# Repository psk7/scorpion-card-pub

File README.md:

## Контроллер периферии для ретро-компьютера Scorpion ZS-256

## Ревизия B:

Подключается к разъему периферии платы компьютера. Позволяет использовать USB клавиатуры, мыши, джойстики, геймпады.

## Ревизия С:
                 
Автономный контроллер USB клавиатуры и геймпада. Не привязан к разъему Scorpion и может
быть использован с любым Spectrum совместимым компьютером, использующим стандартную ZX клавиатуру, но
не имеет поддержки Kempston Mouse и возможностей, обеспечиваемых периферийным разъемом ZS-Scorpion за исключением
клавиатуры и Kempston джойстика.

## Уже реализовано:
- USB-хост: поддержка клавиатур, HID мышей, HID джойстиков/геймпадов, USB хабов
- USB-устройство: подключается к PC, возможно взаимодействие PC со Spectrum
- Безвейтовая ZX-клавиатура с произвольными раскладками, настраиваемыми с PC 
- Reset, Magic с клавиатуры
- Настраиваемые раскладки USB джойстика/геймпада, возможно задействование до 16 кнопок 
- Регенерация синхросмеси. Никаких больше перемычек/разрезов на плате. PAL кодер теперь дает нормальный цветной сигнал
- С доп. платой (в слот шины) USB мышь превращается в Kempston mouse
- Транзитом передает на гребенки: RGB сигнал (с выбором джампером оригинальная/регенерированная синхросмесь), стерео-аудио, моно-аудио, оригинальный видео сигнал, магнитофонный вход/выход, RS-232
- Единая точка подключения питания
- Подключение внешнего джойстика (от Spectrum)
- Настраиваемое отображение кнопок USB джойстика на кнопки ZX клавиатуры/Kempston Joystick
- Управление/индикация на клавиатуре турбой через двухпиновую колодку скорпиона
- Захват centronix в передача на PC
- Проигрыватель tap/tzx с PC через USB порт в Спектрум (`LOAD ""`)
- Транзитная передача с RS232 Скорпиона 
- Поддержка нескольких джойстиков/геймпадов

### Планируется:
- Настройки контроллера (раскладки, мышь, джойстик) через доп. плату нативным приложением для скорпиона

### Недостатки: :smile:
- Нет поддержки PS/2 мышей и клавиатур

## Ревизия А: (Устаревшая)

ВНИМАНИЕ!!! Эта ревизия НЕ РЕКОМЕНДУЕТСЯ К ИЗГОТОВЛЕНИЮ. К сожалению, при проектировании был выбран микроконтроллер не позволяющий реализовать все желаемое по причине нехватки ОЗУ. Готовится к публикации ревизия B, в которой эта проблема устранена.

Файлы для производства удалены из репозитория.

## Содержимое репозитория:
### revB
- cpld - Прошивки микросхем EPM3064
- gerbers - Файлы для производства плат

### revC
- kbd - Прошивка клавиатурной матрицы
- kicad - Проект плат
- atmega - Прошивка управляющего контроллера

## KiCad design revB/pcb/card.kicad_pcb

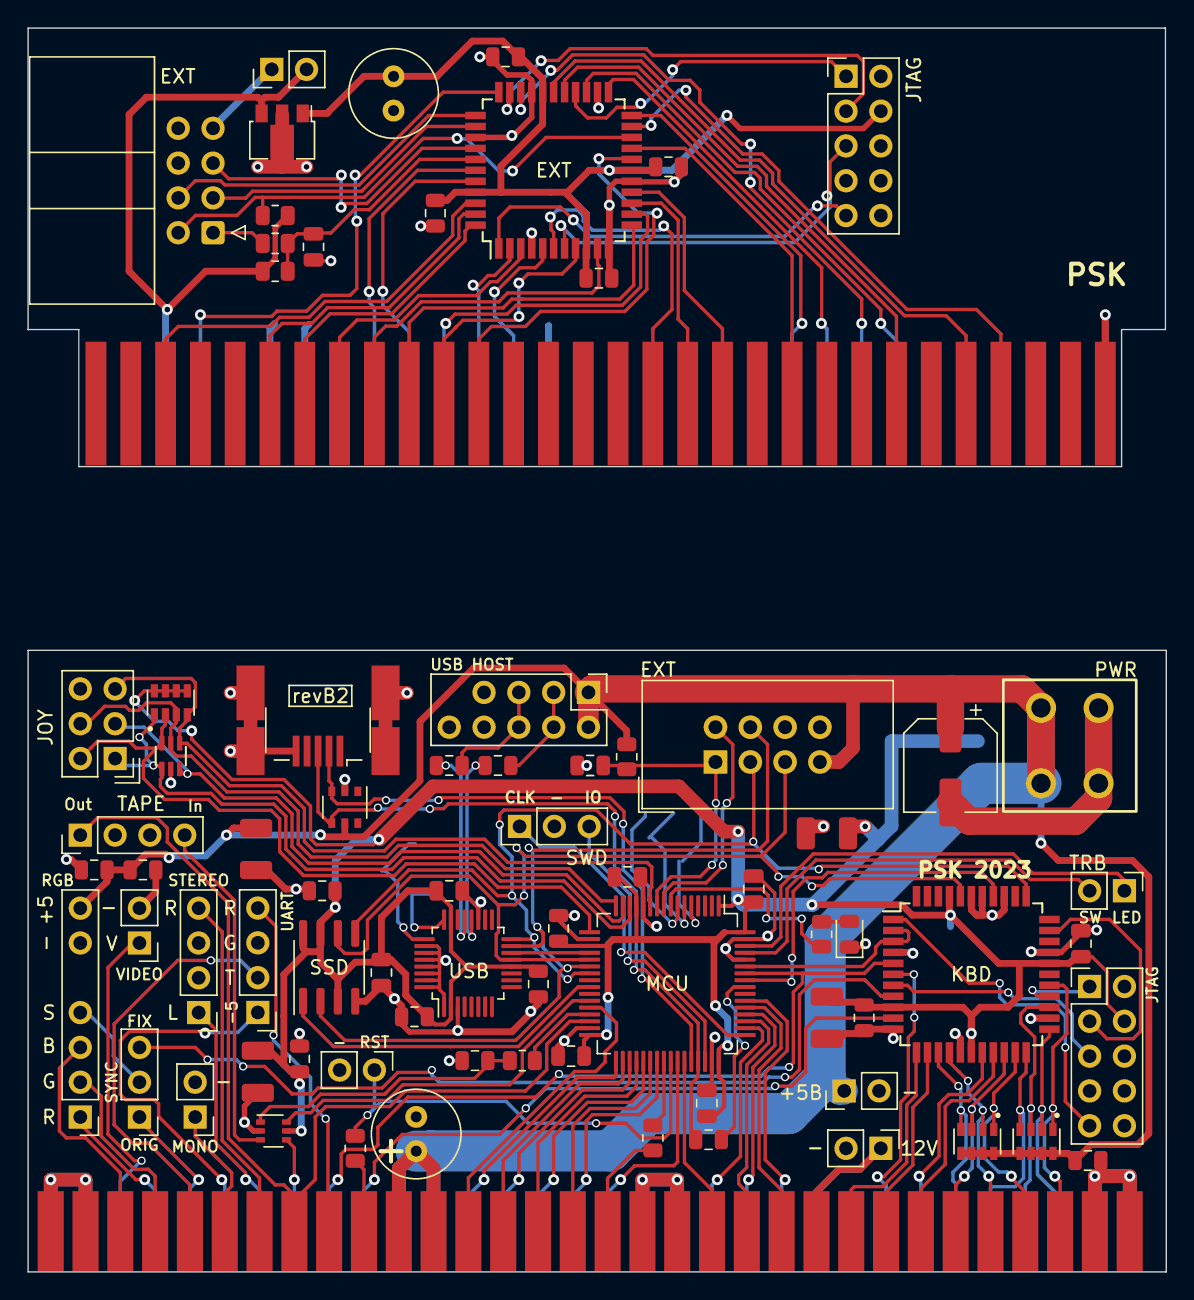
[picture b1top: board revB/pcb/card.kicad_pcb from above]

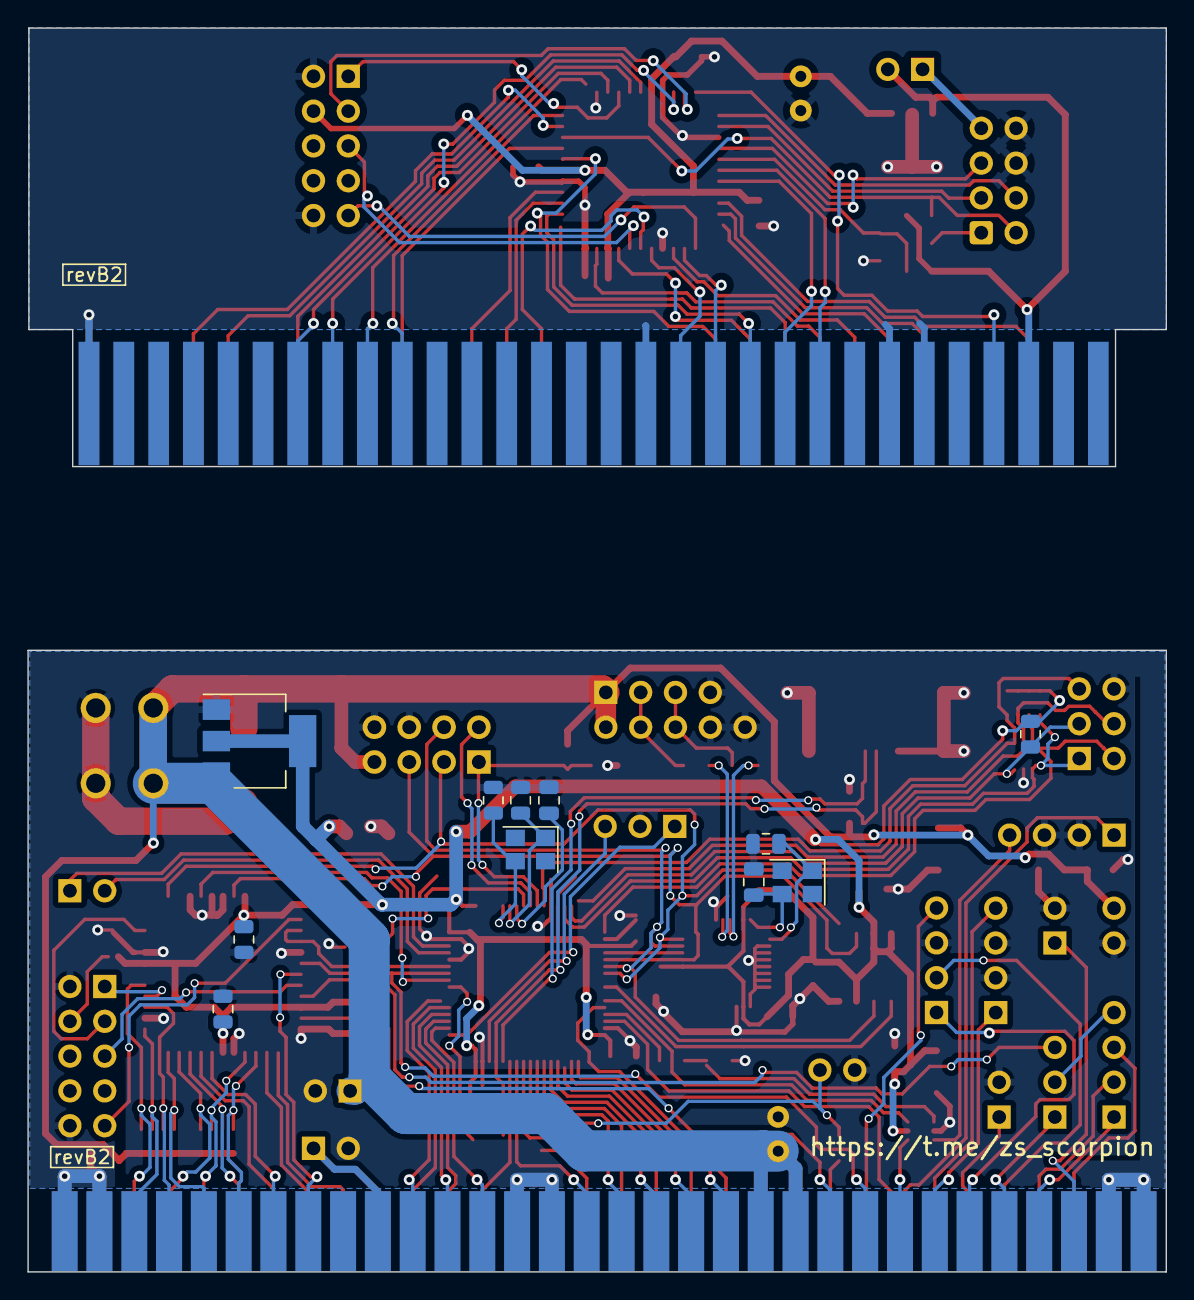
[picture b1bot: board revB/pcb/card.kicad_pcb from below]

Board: 2 copper layers, 83.1 x 45.4 mm, 88 parts (11 on the bottom side), 130 nets.

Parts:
C1, C2, C33, C34: 9p; C_0805_2012Metric
C3, C5, C7, C8, C9, C10, C11, C14, C15, C17, C21, C22, C23, C26, C27, C28, C29, C30, C32, C35, C36: C; C_0805_2012Metric
C4, C12, C18: 4.7uF; C_0805_2012Metric
C6, C24, C25, C31: CP; CP_EIA-3528-12_Kemet-T
C13: CP; CP_Elec_6.3x7.7
C16, C20: CP; C_Radial_D6.3mm_H11.0mm_P2.50mm
C19: 0.1uF; C_0805_2012Metric
D1: LED; LED_0805_2012Metric
J1: USB_B_Mini; usb_mini
J2: SWD; PinHeader_1x03_P2.54mm_Vertical
J3: Conn_01x04; PinHeader_2x05_P2.54mm_Vertical
J4, J6, J7: Conn_01x02; PinHeader_1x02_P2.54mm_Vertical
J5, J10: Conn_01x04; PinHeader_1x04_P2.54mm_Vertical
J8: Conn_01x07_RGB; PinHeader_1x07_P2.54mm_Vertical_RGB
J9: Conn_01x03; PinHeader_1x03_P2.54mm_Vertical
J11: Conn_01x08; IDC-Header_2x04_P2.54mm_Vertical
J12, J15: JTAG; PinHeader_2x05_P2.54mm_Vertical
J13: Conn_02x03_Odd_Even; PinHeader_2x03_P2.54mm_Vertical
J14, J19: +5В; PinHeader_1x02_P2.54mm_Vertical
J16: PWR; pwr
J17: EXT; IDC-Header_2x04_P2.54mm_Horizontal
J18: UART; PinHeader_1x04_P2.54mm_Vertical
J20: 3V3; PinHeader_1x02_P2.54mm_Vertical
J21: Conn_01x01_Male; PinHeader_1x02_P2.54mm_Vertical
R1, R2: 33; R_0805_2012Metric
R3: 1k5; R_0805_2012Metric
R4, R7: 0; R_0805_2012Metric
R5, R11: 1K; R_0805_2012Metric
R6, R12: 1k; R_0805_2012Metric
R8: 1k2; R_0805_2012Metric
R9, R13: 250; R_0805_2012Metric
R14: -; R_0805_2012Metric
RN1, RN2, RN3: 4x1k2; RESCAF80P320X160X60-8N
U1: STM32F103R8; LQFP-64_10x10mm_P0.5mm
U2: EPM3064; TQFP-44_10x10mm_P0.8mm
U3: MAX3421EEHJ+T; LQFP-32_5x5mm_P0.5mm
U4: IP4220CZ6; TSOP-6_1.65x3.05mm_P0.95mm
U5: 25LC256T; SOIC-8_3.9x4.9mm_P1.27mm
U7: EXT; TQFP-44_10x10mm_P0.8mm
U8: L78L33; SOT-89-3
U9: SMF05CT1G; SOT65P210X110-6N
U10: LD1117S33TR; SOT-223-3_TabPin2
U11: TS5A3159DCK; SOT-363_SC-70-6
X1: ScorpionEdgeConnector; PADS_2.5_32
X2: ScorpionBusConnector; PADS_2.5_32
Y1, Y2: 12MHz; Crystal_SMD_3225-4Pin_3.2x2.5mm

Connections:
+3.3V: C20.1, C22.1, C27.1, C28.1, C29.1, J12.4, U7.9 (VCC), U7.17 (VCC), U7.29 (VCC), U7.41 (VCC), U8.1 (OUT)
+3V3: C3.1, C4.1, C5.1, C6.1, C7.1, C8.1, C9.1, C10.1, C11.1, C12.1, C14.1, C15.1, C18.1, C24.1, C25.1, C26.1, C30.1, C35.1, J15.4, R8.1, RN3.5, RN3.6, RN3.7, RN3.8, U1.1 (VBAT), U1.13 (VDDA), U1.19 (VDD), U1.32 (VDD), U1.48 (VDD), U1.64 (VDD), U2.9 (VCC), U2.17 (VCC), U2.29 (VCC), U2.41 (VCC), U3.2 (VL), U3.12 (~RES), U3.23 (VCC), U5.3 (~WP), U5.7 (~HOLD), U5.8 (VCC), U10.2 (VO), U11.5 (V+)
+5V: C13.1, C16.1, C17.1, C21.1, C23.1, C31.1, J3.1, J3.6, J8.7, J11.7, J14.1, J16.1, J16.2, J19.2, R5.2, R6.1, R12.1, RN1.5, RN1.6, RN1.7, RN1.8, RN2.5, RN2.6, RN2.7, RN2.8, U4.5 (Vbus), U8.3 (IN), U10.3 (VI), X1.21 (+5V), X1.22 (+5V), X1.23 (+5V), X1.24 (+5V), X2.6 (+5V)
+12V: J6.1, X1.45 (+12V), X1.46 (+12V)
-5V: J18.1, X1.12 (+5V)
/ExtCard/TCK: J12.1, U7.26 (TCK)
/ExtCard/TDI: J12.9, U7.1 (TDI)
/ExtCard/TDO: J12.3, U7.32 (TDO)
/ExtCard/TMS: J12.5, U7.7 (TMS)
/LED2: R11.2, U1.8 (PC0)
/MAGIC: R13.1, U1.40 (PC9)
/STGSS: U1.25 (PC5), U5.1 (~CS)
/SWDCLK: J2.1, U1.49 (PA14)
/SWDIO: J2.3, U1.46 (PA13)
/TCK: J15.1, U2.26 (TCK)
/TDI: J15.9, U2.1 (TDI)
/TDO: J15.3, U2.32 (TDO)
/TMS: J15.5, U2.7 (TMS)
/USBC_DM: J1.2 (D-), U1.44 (PA11), U4.3 (D-)
/USBC_DP: J1.3 (D+), R3.2, U1.45 (PA12), U4.4 (D+)
/USBH_DM: J3.2, J3.7, R2.2
/USBH_DP: J3.3, J3.8, R1.2
/USB_PULLUP: R3.1, U1.56 (PB4)
/USS: U1.20 (PA4), U3.14 (~SS)
A0: U7.39 (A0), X2.18 (A0)
A1: U7.40 (A1), X2.20 (A1)
A2: U7.13 (A2), X2.22 (A2)
A3: U7.2 (A3), X2.24 (A3)
A4: U7.25 (A4), X2.48 (A4)
A5: U7.31 (A5), X2.46 (A5)
A6: U7.23 (A6), X2.44 (A6)
A7: U7.22 (A7), X2.42 (A7)
A8: U7.28 (A8), X2.51 (A8)
A10: U7.21 (A10), X2.53 (A10)
B: J8.3, X1.5 (B)
CC: U1.58 (PB6), U2.5 (KC), X1.18 ((CC))
CN0: U1.36 (PB15), X1.29 (Centr_0)
CN1: U1.39 (PC8), X1.32 (Centr_1)
CN2: U1.38 (PC7), X1.31 (Centr_2)
CN3: U1.34 (PB13), X1.27 (Centr_3)
CN4: U1.28 (PB2), X1.25 (Centr_4)
CN5: U1.37 (PC6), X1.30 (Centr_5)
CN6: U1.33 (PB12), X1.26 (Centr_6)
CN7: U1.35 (PB14), X1.28 (Centr_7)
CNBUSY: U1.43 (PA10), X1.39 (BUSY)
CNSTB: U1.42 (PA9), X1.34 (Strobe)
D0: U7.43 (D0), X2.11 (D0)
D1: U7.44 (D1), X2.13 (D1)
D2: U7.3 (D2), X2.15 (D2)
D3: U7.8 (D3), X2.21 (D3)
D4: U7.18 (D4), X2.23 (D4)
D5: U7.12 (D5), X2.19 (D5)
D6: U7.10 (D6), X2.17 (D6)
D7: U7.42 (D7), X2.5 (D7)
DELAY_IN: U1.59 (PB7), U2.2 (DELAY_IN2), U2.3 (DELAY_IN)
DOS: U7.33 (DOS), X2.8 (DOS)
DSR: J18.4, X1.17 (DSR)
EINT: J11.2, U1.9 (PC1)
EINT_E: J17.2, R12.2, U7.20 (INT)
ESS: C36.2, J11.1, R5.1, U1.10 (PC2)
ESS_E: C32.2, R4.1, R6.2, U7.38 (SS)
G: J8.2, X1.7 (G)
GND: C1.2, C2.2, C3.2, C4.2, C5.2, C6.2, C7.2, C8.2, C9.2, C10.2, C11.2, C12.2, C13.2, C14.2, C15.2, C16.2, C17.2, C18.2, C19.2, C20.2, C21.2, C22.2, C23.2, C24.2, C25.2, C26.2, C27.2, C28.2, C29.2, C30.2, C31.2, C32.1, C33.2, C34.2, C35.2, C36.1, D1.1 (K), J1.5 (GND), J1.6 (Shield), J2.2, J3.4, J3.9, J3.10, J4.2, J5.2, J5.3, J6.2, J7.2, J8.6, J10.2, J10.3, J11.6, J11.8, J12.2, J12.10, J13.6, J14.2, J15.2, J15.10, J16.3, J16.4, J17.6, J17.8, J18.3, J21.2, R7.1, U1.12 (VSSA), U1.18 (VSS), U1.31 (VSS), U1.47 (VSS), U1.60 (BOOT0), U1.63 (VSS), U2.4 (GND), U2.11 (GND), U2.16 (GND), U2.24 (GND), U2.30 (GND), U2.36 (GND), U2.38 (UNUSED), U2.39 (UNUSED), U3.1 (GPIN7), U3.3 (GND), U3.19 (GND), U3.26 (GPIN0), U3.27 (GPIN1), U3.28 (GPIN2), U3.29 (GPIN3), U3.30 (GPIN4), U3.31 (GPIN5), U3.32 (GPIN6), U4.2 (GND), U5.4 (GND), U7.4 (GND), U7.11 (GND), U7.16 (GND), U7.24 (GND), U7.30 (GND), U7.36 (GND), U8.2 (GND), U9.2, U10.1 (GND), U11.2 (GND), X1.1 (GND), X1.2 (GND), X1.3 (GND), X1.4 (GND), X1.35 (GND), X1.36 (GND), X1.37 (GND), X1.38 (GND), X1.61 (GND), X1.62 (GND), X1.63 (GND), X1.64 (GND), X2.12 (GND), X2.14 (GND), X2.28 (GND), X2.59 (GND), X2.60 (GND)
IJ0: J13.1, RN3.1, U1.14 (PA0), U9.1
IJ1: J13.2, RN3.2, U1.17 (PA3), U9.6
IJ2: J13.3, R8.2, U1.15 (PA1), U9.3
IJ3: J13.4, RN3.3, U1.16 (PA2), U9.5
IJ4: J13.5, RN3.4, U1.11 (PC3), U9.4
IORQ: U7.6 (IORQ), X2.33 (IORQ)
IORQGE: U7.5 (IORQGE), X2.26 (IORQGE)
ITIN: J10.4, U11.3
J0: U1.51 (PC10), X1.41 (Kemps_0)
J1: U1.52 (PC11), X1.42 (Kemps_1)
J2: U1.54 (PD2), X1.44 (Kemps_2)
J3: U1.53 (PC12), X1.43 (Kemps_3)
J4: U1.50 (PA15), X1.40 (Kemps_4)
KA0: RN2.4, U2.14 (KA0), X1.54 (Kb_a8)
KA1: RN2.3, U2.20 (KA1), X1.53 (Kb_a9)
KA2: RN2.2, U2.15 (KA2), X1.55 (Kb_a10)
KA3: RN1.4, U2.22 (KA3), X1.56 (Kb_a11)
KA4: RN2.1, U2.21 (KA4), X1.57 (Kb_a12)
KA5: RN1.3, U2.25 (KA5), X1.58 (Kb_a13)
KA6: RN1.1, U2.27 (KA6), X1.59 (Kb_a14)
KA7: RN1.2, U2.23 (KA7), X1.60 (Kb_a15)
KBSS: U1.57 (PB5), U2.37 (SS)
KC: U2.10 (CC), X1.20 ((KC))
KD0: U2.19 (KD0), X1.51 (Kb_in0)
KD1: U2.18 (KD1), X1.52 (Kb_in1)
KD2: U2.13 (KD2), X1.49 (Kb_in2)
KD3: U2.6 (KD3), X1.50 (Kb_in3)
KD4: U2.12 (KD4), X1.47 (Kb_in4)
LEFT: J5.1, X1.14 (LEFT)
M1: U7.27 (M1), X2.47 (M1)
MC_RES: C19.1, U1.7 (NRST)
MISO: J11.4, U1.22 (PA6), U3.15 (MISO), U5.2 (MISO)
MISO5_E: J17.4, U7.34 (MISO)
MOSI: J11.3, U1.23 (PA7), U2.34 (DI), U3.16 (MOSI), U5.5 (MOSI)
MOSI5_E: J17.3, U7.35 (MOSI)
NMI: R13.2, X1.33 (MAGIC)
unnamed: D1.2 (A), R11.1
unnamed: J17.1, R4.2
unnamed: J17.7, J19.1
unnamed: J21.1, R9.2, U1.41 (PA8)
unnamed: R7.2, R14.1, U11.1
unnamed: R14.2, U1.29 (PB10)
unnamed: C2.1, U1.5 (PD0), Y2.3
unnamed: C1.1, U1.6 (PD1), Y2.1
unnamed: R1.1, U3.21 (D+)
unnamed: R2.1, U3.20 (D-)
unnamed: C33.1, U3.24 (XI), Y1.3
unnamed: C34.1, U3.25 (XO), Y1.1
OSYNC: J8.4, J9.2
OUT_SYNC: J9.3, U2.8 (OUT_SYNC)
R: J8.1, X1.8 (R)
RD: U7.14 (RD), X2.35 (RD)
RIGHT: J5.4, X1.13 (RIGHT)
SCK: J11.5, U1.21 (PA5), U2.40 (CLK), U3.13 (SCLK), U5.6 (SCK)
SCK5_E: J17.5, U7.37 (SCK)
SOUND: J7.1, X1.11 (SOUND)
SYNC: J9.1, X1.10 (SYNC)
TIN: U11.4, X1.16 (TAPE_IN)
TINC: U1.27 (PB1), U11.6
TOUT: J10.1, U1.30 (PB11), X1.15 (TAPE_OUT)
TRBLED: J20.1, U1.62 (PB9)
TRBSW: J20.2, U1.61 (PB8)
TXD: J18.2, X1.9 (TxD)
VIDEO: J4.1, X1.6 (VIDEO)
WAIT: U7.19 (WAIT), X2.41 (WAIT)
WR: U7.15 (WR), X2.37 (WR)
ZRES: R9.1, X1.19 (RESET)

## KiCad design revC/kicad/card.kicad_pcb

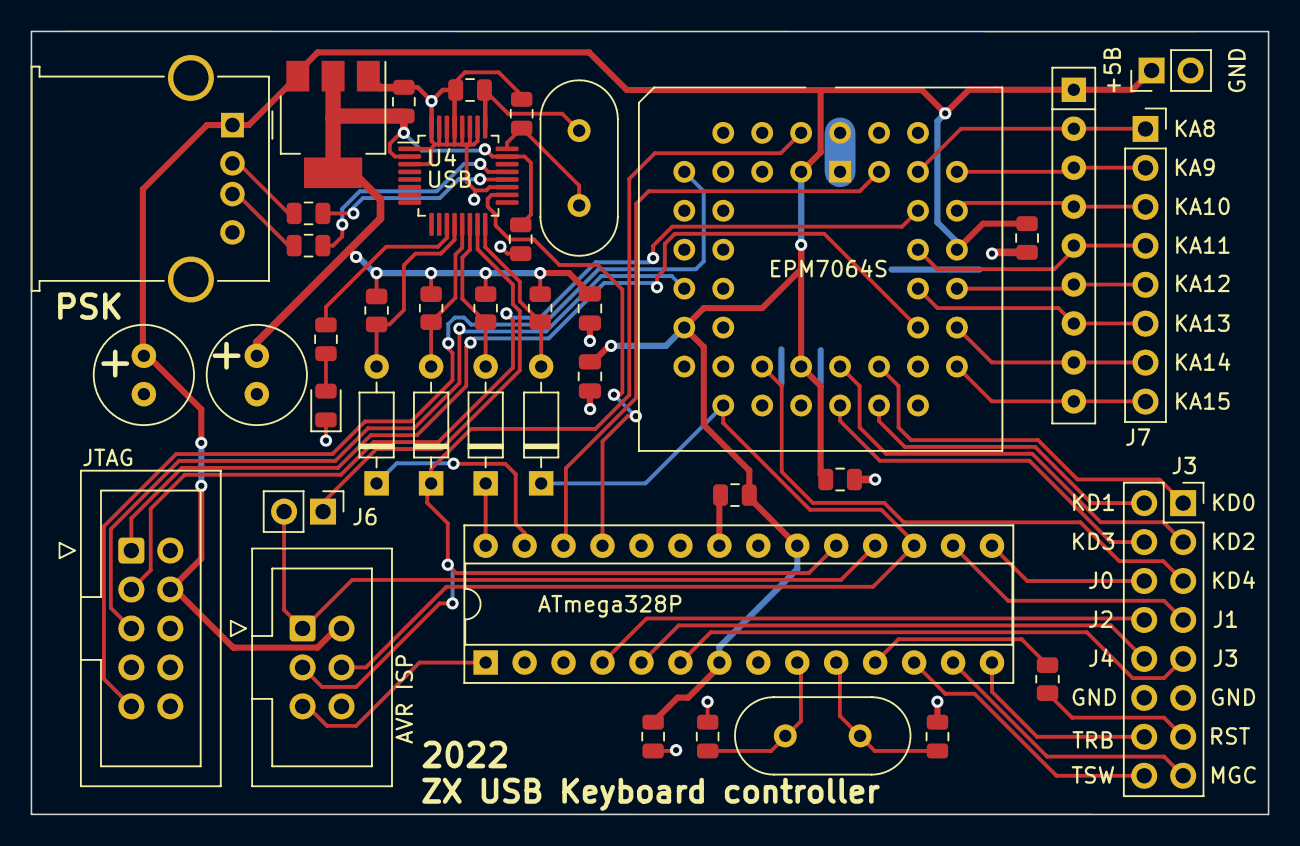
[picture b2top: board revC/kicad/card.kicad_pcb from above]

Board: 2 copper layers, 80.7 x 51.1 mm, 41 parts (0 on the bottom side), 53 nets.

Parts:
C1, C2, C3, C4: 10p; C_0805_2012Metric
C5, C7, C9, C10, C11, C12, C13, C14: 0.1u; C_0805_2012Metric
C6, C8: 100u x 16В; C_Radial_D6.3mm_H11.0mm_P2.50mm
D1, D2, D3, D5: BAT43; D_DO-35_SOD27_P7.62mm_Horizontal
D4: LED; LED_0805_2012Metric
J1: AVR ISP; IDC-Header_2x03_P2.54mm_Vertical
J2: JTAG; IDC-Header_2x05_P2.54mm_Vertical
J3: Conn_02x08_Odd_Even; PinSocket_2x08_P2.54mm_Vertical
J4: Conn_01x04; USB_A_Molex_67643_Horizontal
J5: PWR; PinHeader_1x02_P2.54mm_Vertical
J6: PROG; PinHeader_1x02_P2.54mm_Vertical
J7: ADDR; PinSocket_1x08_P2.54mm_Vertical
R1: 200; R_0805_2012Metric
R2, R3, R4, R8: 750; R_0805_2012Metric
R5, R6: 33; R_0805_2012Metric
R7: 1K; R_0805_2012Metric
RN1: 8x4k7; R_Array_SIP9
U1: LD1117S33TR_SOT223; SOT-223-3_TabPin2
U2: ATmega328P; DIP-28_W7.62mm_Socket
U3: EPM7064S; PLCC-44_THT-Socket
U4: MAX3421EEHJ+T; LQFP-32_5x5mm_P0.5mm
Y1: 16M; Crystal_HC49-4H_Vertical
Y2: 12M; Crystal_HC49-4H_Vertical

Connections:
+3V3: C5.1, C6.1, C7.1, C11.1, R2.1, R3.1, R4.1, R8.1, U1.2 (VO), U4.2 (VL), U4.23 (VCC)
+5V: C8.1, C9.1, C10.1, C12.1, C13.1, C14.1, J1.2, J2.4, J4.1, J5.1, RN1.1 (common), U1.3 (VI), U2.7 (VCC), U2.20 (AVCC), U3.3 (VCC), U3.15 (VCC), U3.23 (VCC), U3.35 (VCC)
/TCK: J2.1, U3.32 (TCK)
/TDI: J2.9, U3.7 (TDI)
/TDO: J2.3, U3.38 (TDO)
/TMS: J2.5, U3.13 (TMS)
GND: C1.2, C2.2, C3.2, C4.2, C5.2, C6.2, C7.2, C8.2, C9.2, C10.2, C11.2, C12.2, C13.2, C14.2, D4.1 (K), J1.6, J2.2, J2.10, J3.11, J3.12, J4.4, J4.5 (Pin_4), J5.2, U1.1 (GND), U2.8 (GND), U2.22 (GND), U3.1 (GND), U3.10 (GND), U3.22 (GND), U3.30 (GND), U3.42 (GND), U3.44 (GND), U4.1 (GPIN7), U4.3 (GND), U4.19 (GND), U4.26 (GPIN0), U4.27 (GPIN1), U4.28 (GPIN2), U4.29 (GPIN3), U4.30 (GPIN4), U4.31 (GPIN5), U4.32 (GPIN6)
J0: J3.6, U2.15 (PB1)
J1: J3.7, U2.16 (PB2)
J2: J3.8, U2.4 (PD2)
J3: J3.9, U2.6 (PD4)
J4: J3.10, U2.5 (PD3)
KA0: J7.1, RN1.2 (R1), U3.41 (KA0)
KA1: J7.2, RN1.3 (R2), U3.39 (KA1)
KA2: J7.3, RN1.4 (R3), U3.37 (KA2)
KA3: J7.4, RN1.5 (R4), U3.36 (KA3)
KA4: J7.5, RN1.6 (R5), U3.33 (KA4)
KA5: J7.6, RN1.7 (R6), U3.34 (KA5)
KA6: J7.7, RN1.8 (R7), U3.31 (KA6)
KA7: J7.8, RN1.9 (R8), U3.29 (KA7)
KD0: J3.1, U3.27 (KD0)
KD1: J3.2, U3.26 (KD1)
KD2: J3.3, U3.25 (KD2)
KD3: J3.4, U3.24 (KD3)
KD4: J3.5, U3.21 (KD4)
MC_RES: J1.5, U2.1 (PC6/~RESET)
MISO: J1.1, J6.2, U2.18 (MISO/PB4)
MOSI: D5.1 (K), J1.4, U2.17 (MOSI/PB3), U3.18 (MOSI)
NMI: J3.15, U2.13 (PD7)
unnamed: C1.1, U2.9 (PB6/XTAL1), Y1.1
unnamed: C2.1, U2.10 (PB7/XTAL2), Y1.2
unnamed: C3.1, U4.24 (XI), Y2.1
unnamed: C4.1, U4.25 (XO), Y2.2
unnamed: D1.2 (A), R2.2, U4.13 (SCLK)
unnamed: D2.2 (A), R3.2, U4.12 (~RES)
unnamed: D3.2 (A), R4.2, U4.14 (~SS)
unnamed: D4.2 (A), R7.1
unnamed: D5.2 (A), R8.2, U4.16 (MOSI)
unnamed: J4.2, R6.2
unnamed: J4.3, R5.2
unnamed: J6.1, U4.15 (MISO)
unnamed: R1.2, U2.11 (PD5)
unnamed: R5.1, U4.21 (D+)
unnamed: R6.1, U4.20 (D-)
unnamed: R7.2, U4.11 (GPOUT7)
RST: J3.13, R1.1
SCK: D1.1 (K), J1.3, U2.19 (SCK/PB5), U3.2 (SCK)
TRBLED: J3.14, U2.14 (PB0)
TRBSW: J3.16, U2.12 (PD6)
UINT: U2.25 (PC2), U4.18 (INT)
~KBSS: U2.26 (PC3), U3.43 (CS)
~URES: D2.1 (K), U2.27 (PC4)
~USS: D3.1 (K), U2.28 (PC5)

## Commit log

2022-06-15 Initial
2022-06-16 Layout
2022-06-16 Incomplete atmega sources added
2022-06-16 Readme
2022-06-17 Sources updated
2022-07-30 Readme updated
2023-01-07 revC added
2023-01-07 revA moved
2023-01-07 README.md updated
2023-01-08 Create LICENSE
2023-01-08 LUFA License added
2023-01-08 revC atmega sources added
2023-01-08 revC atmega compiled firmware updated
2023-01-08 revC atmega firmware updated
2023-01-09 Cleanup
2023-01-09 Gerbers added
2023-01-09 Documents added
2023-01-10 Schematic added
2023-04-06 revC special Mikka_A edition added
2023-04-06 Compiled firmware added
2023-04-08 Some optimizations
2023-06-11 revB
2023-06-14 Документация для производства
2023-09-10 Добавлено ПО управляющего микроконтроллера
2023-09-10 Добавлена программа сервисного обслуживания
2023-09-14 Добавлены исходники платы
2023-11-19 Обновлена программа сервисного обслуживания. Обновлено ПО управляющего микроконтроллера. Исправлены некоторые ошибки записи макроса.
2024-04-12 Добавлен INF драйвер CDC для Windows 7
